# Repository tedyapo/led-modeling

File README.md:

# led-modeling
Automated LED analysis and SPICE model generation

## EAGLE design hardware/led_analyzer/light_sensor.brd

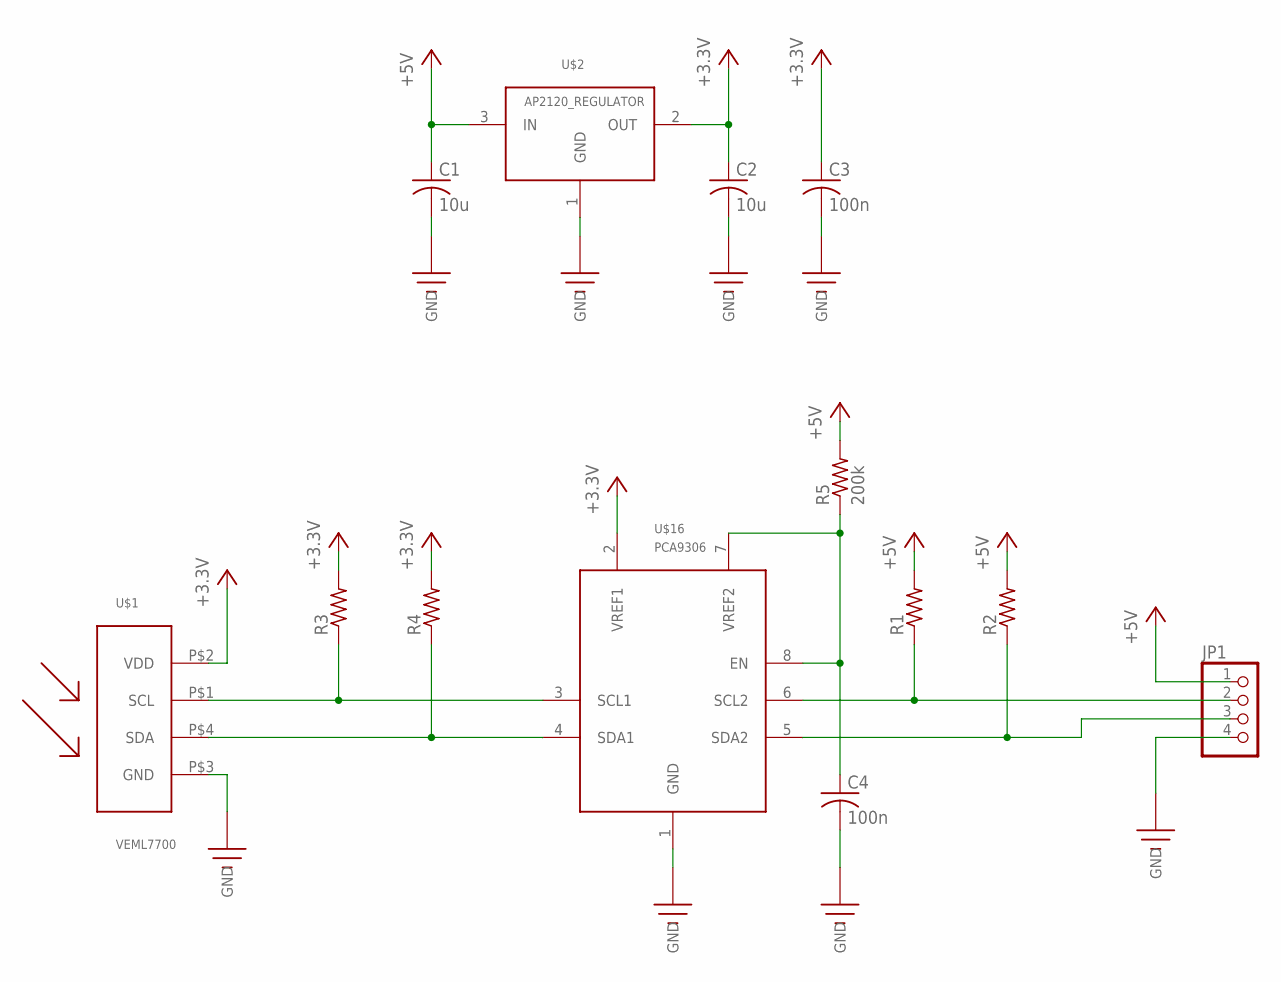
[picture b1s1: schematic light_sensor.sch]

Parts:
C1, C2: 10u; C1206K
C3, C4: 100n; C0603K
JP1: PINHD-1X4; 1X04
R1, R2, R3, R4: R-US_R0603; R0603
R5: 200k; R0603
U$1: VEML7700; VEML7700_SIDE
U$2: AP2120_REGULATOR; SOT23
U$16: PCA9306; SO08

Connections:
+3.3V: C2.1, C3.1, R3.2, R4.2, U$1.P$2 (VDD), U$2.2 (OUT), U$16.2 (VREF1)
+5V: C1.1, JP1.1, R1.2, R2.2, R5.2, U$2.3 (IN)
GND: C1.2, C2.2, C3.2, C4.2, JP1.4, U$1.P$3 (GND), U$2.1 (GND), U$16.1 (GND)
unnamed: R4.1, U$1.P$4 (SDA), U$16.4 (SDA1)
unnamed: R3.1, U$1.P$1 (SCL), U$16.3 (SCL1)
unnamed: JP1.3, R2.1, U$16.5 (SDA2)
unnamed: JP1.2, R1.1, U$16.6 (SCL2)
unnamed: C4.1, R5.1, U$16.7 (VREF2), U$16.8 (EN)

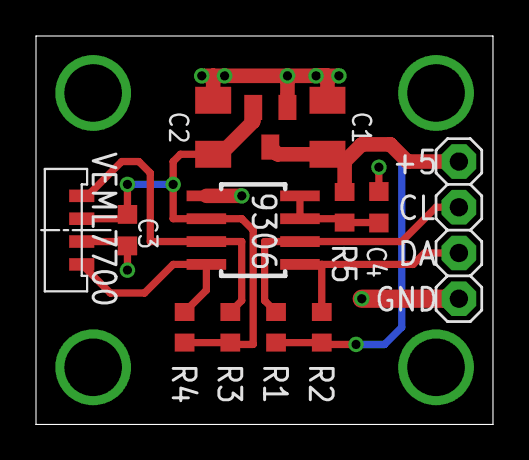
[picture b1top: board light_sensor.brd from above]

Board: 2 copper layers, 25.4 x 21.6 mm, 13 parts (0 on the bottom side), 8 nets.

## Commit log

2016-07-27 Initial commit for light sensor board * added light sensor board withh VEML7700 and I2C level shifter * updated copyright notice in license file
2016-10-31 Added initial SPICE model generation code
2016-10-31 fixed confusing filenames
